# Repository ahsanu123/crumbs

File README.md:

- Hardware Status ✔️ Production Done
- Hardware Status 🏁 Prototype Done
- Software Status ☑️ Finished
- Software Status ⭐ POC only
- ⏳ In Progress

| Name                                                     | Hardware Status  | Software Status | Enclosure       | 
|----------------------------------------------------------|------------------|-----------------|-----------------|
|  TMD - Temperature Measurement Dongle                    |       🏁         |       ⭐        |     ⏳          |

## References 

- [ESP32 S3 Series IO MUX Map](https://documentation.espressif.com/esp32-s3_datasheet_en.pdf)
- [Emi's Reverse Engineer HCSR04](https://uglyduck.vajn.icu/ep/archive/2014/01/Making_a_better_HC_SR04_Echo_Locator.html)

<sub>a long project with the hope of completion. created with ♥️ by ah...</sub>

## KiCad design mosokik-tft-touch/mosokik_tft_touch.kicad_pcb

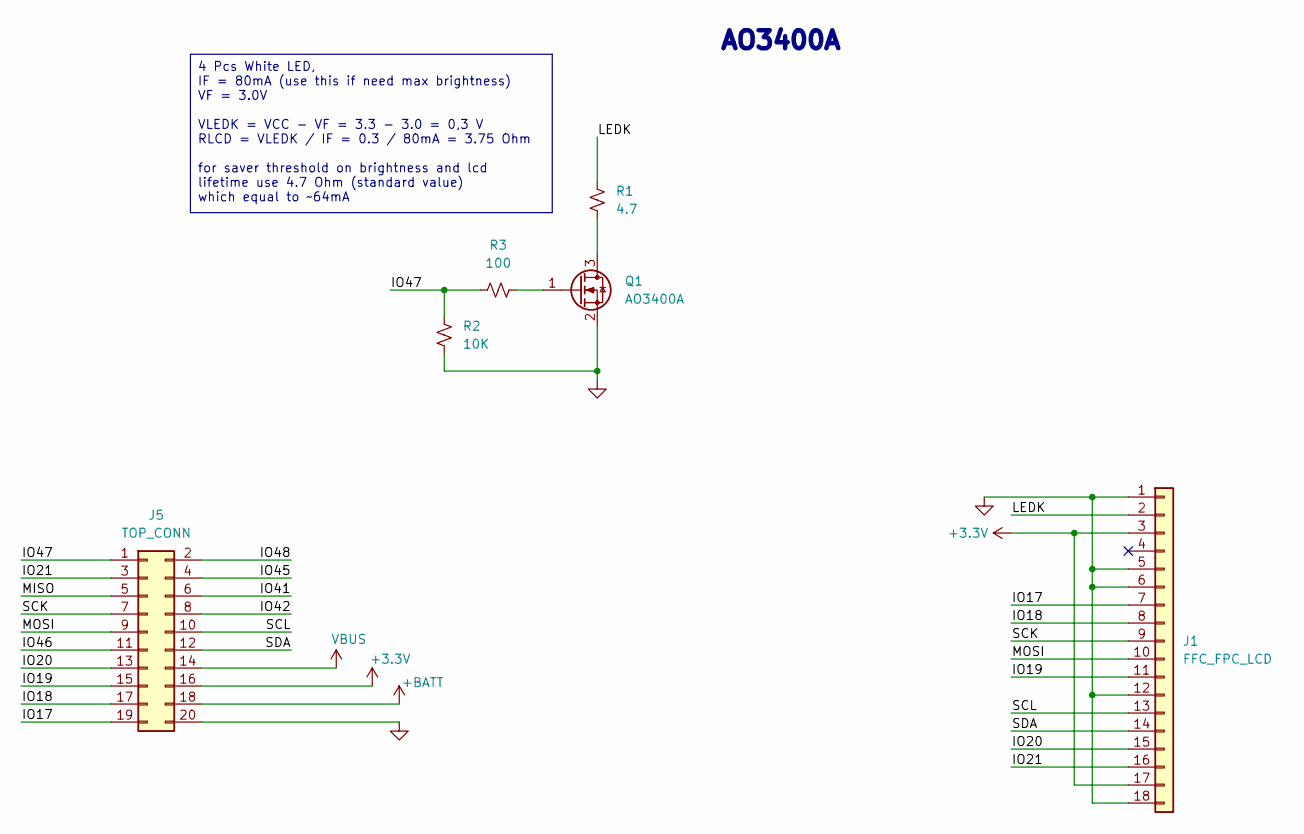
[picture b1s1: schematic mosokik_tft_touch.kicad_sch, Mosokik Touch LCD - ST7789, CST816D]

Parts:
J1: FFC_FPC_LCD; Hirose_FH12-18S-0.5SH_1x18-1MP_P0.50mm_Horizontal
J5: TOP_CONN; PinHeader_2x10_P2.54mm_Horizontal
Q1: AO3400A; SOT-23
R1: 4.7; R_0805_2012Metric
R2: 10K; R_0805_2012Metric
R3: 100; R_0805_2012Metric

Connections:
+3.3V: J1.3, J1.17, J5.16
+BATT: J5.18
/IO17: J1.7, J5.19
/IO18: J1.8, J5.17
/IO19: J1.11, J5.15
/IO20: J1.15, J5.13
/IO21: J1.16, J5.3
/IO41: J5.6
/IO42: J5.8
/IO45: J5.4
/IO46: J5.11
/IO47: J5.1, R2.1, R3.1
/IO48: J5.2
/LEDK: J1.2, R1.1
/MISO: J5.5
/MOSI: J1.10, J5.9
/SCK: J1.9, J5.7
/SCL: J1.13, J5.10
/SDA: J1.14, J5.12
GND: J1.1, J1.5, J1.6, J1.12, J1.18, J5.20, Q1.2 (S), R2.2
unnamed: Q1.3 (D), R1.2
unnamed: Q1.1 (G), R3.2
VBUS: J5.14

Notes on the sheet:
AO3400A
4 Pcs White LED, IF = 80mA (use this if need max brightness) VF = 3.0V VLEDK = VCC - VF = 3.3 - 3.0 = 0,3 V RLCD = VLEDK / IF = 0.3 / 80mA = 3.75 Ohm for saver threshold on brightness and lcd lifetime use 4.7 Ohm (standard value) which equal to ~64mA

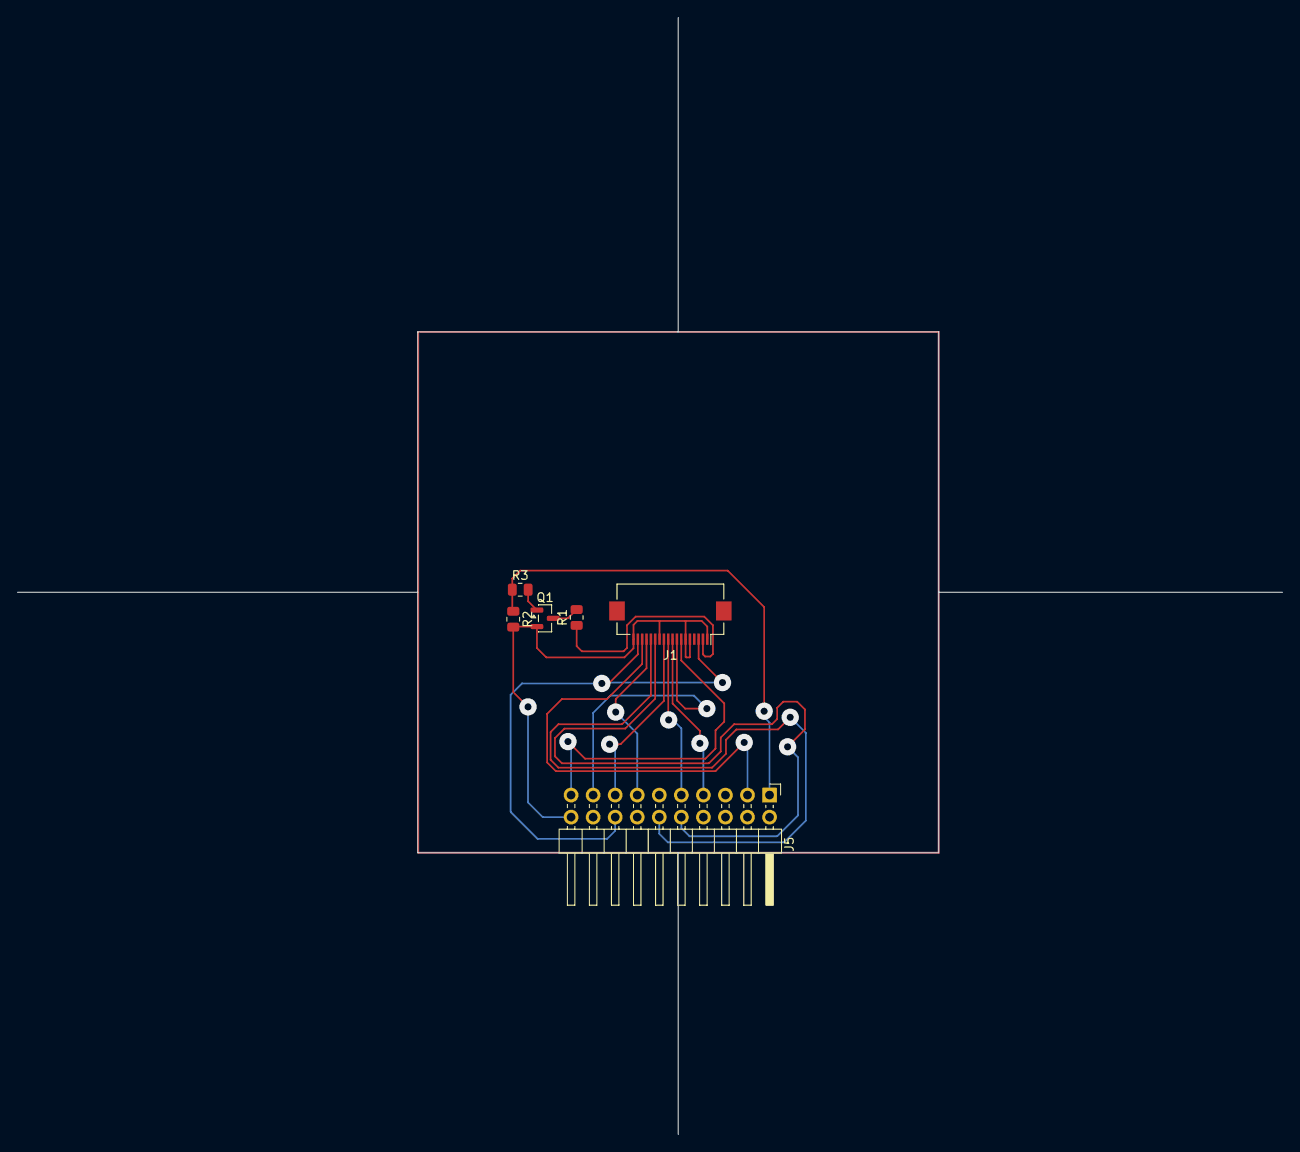
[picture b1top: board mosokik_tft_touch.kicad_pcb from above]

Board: 2 copper layers, 60.0 x 60.0 mm, 6 parts (0 on the bottom side), 15 nets.

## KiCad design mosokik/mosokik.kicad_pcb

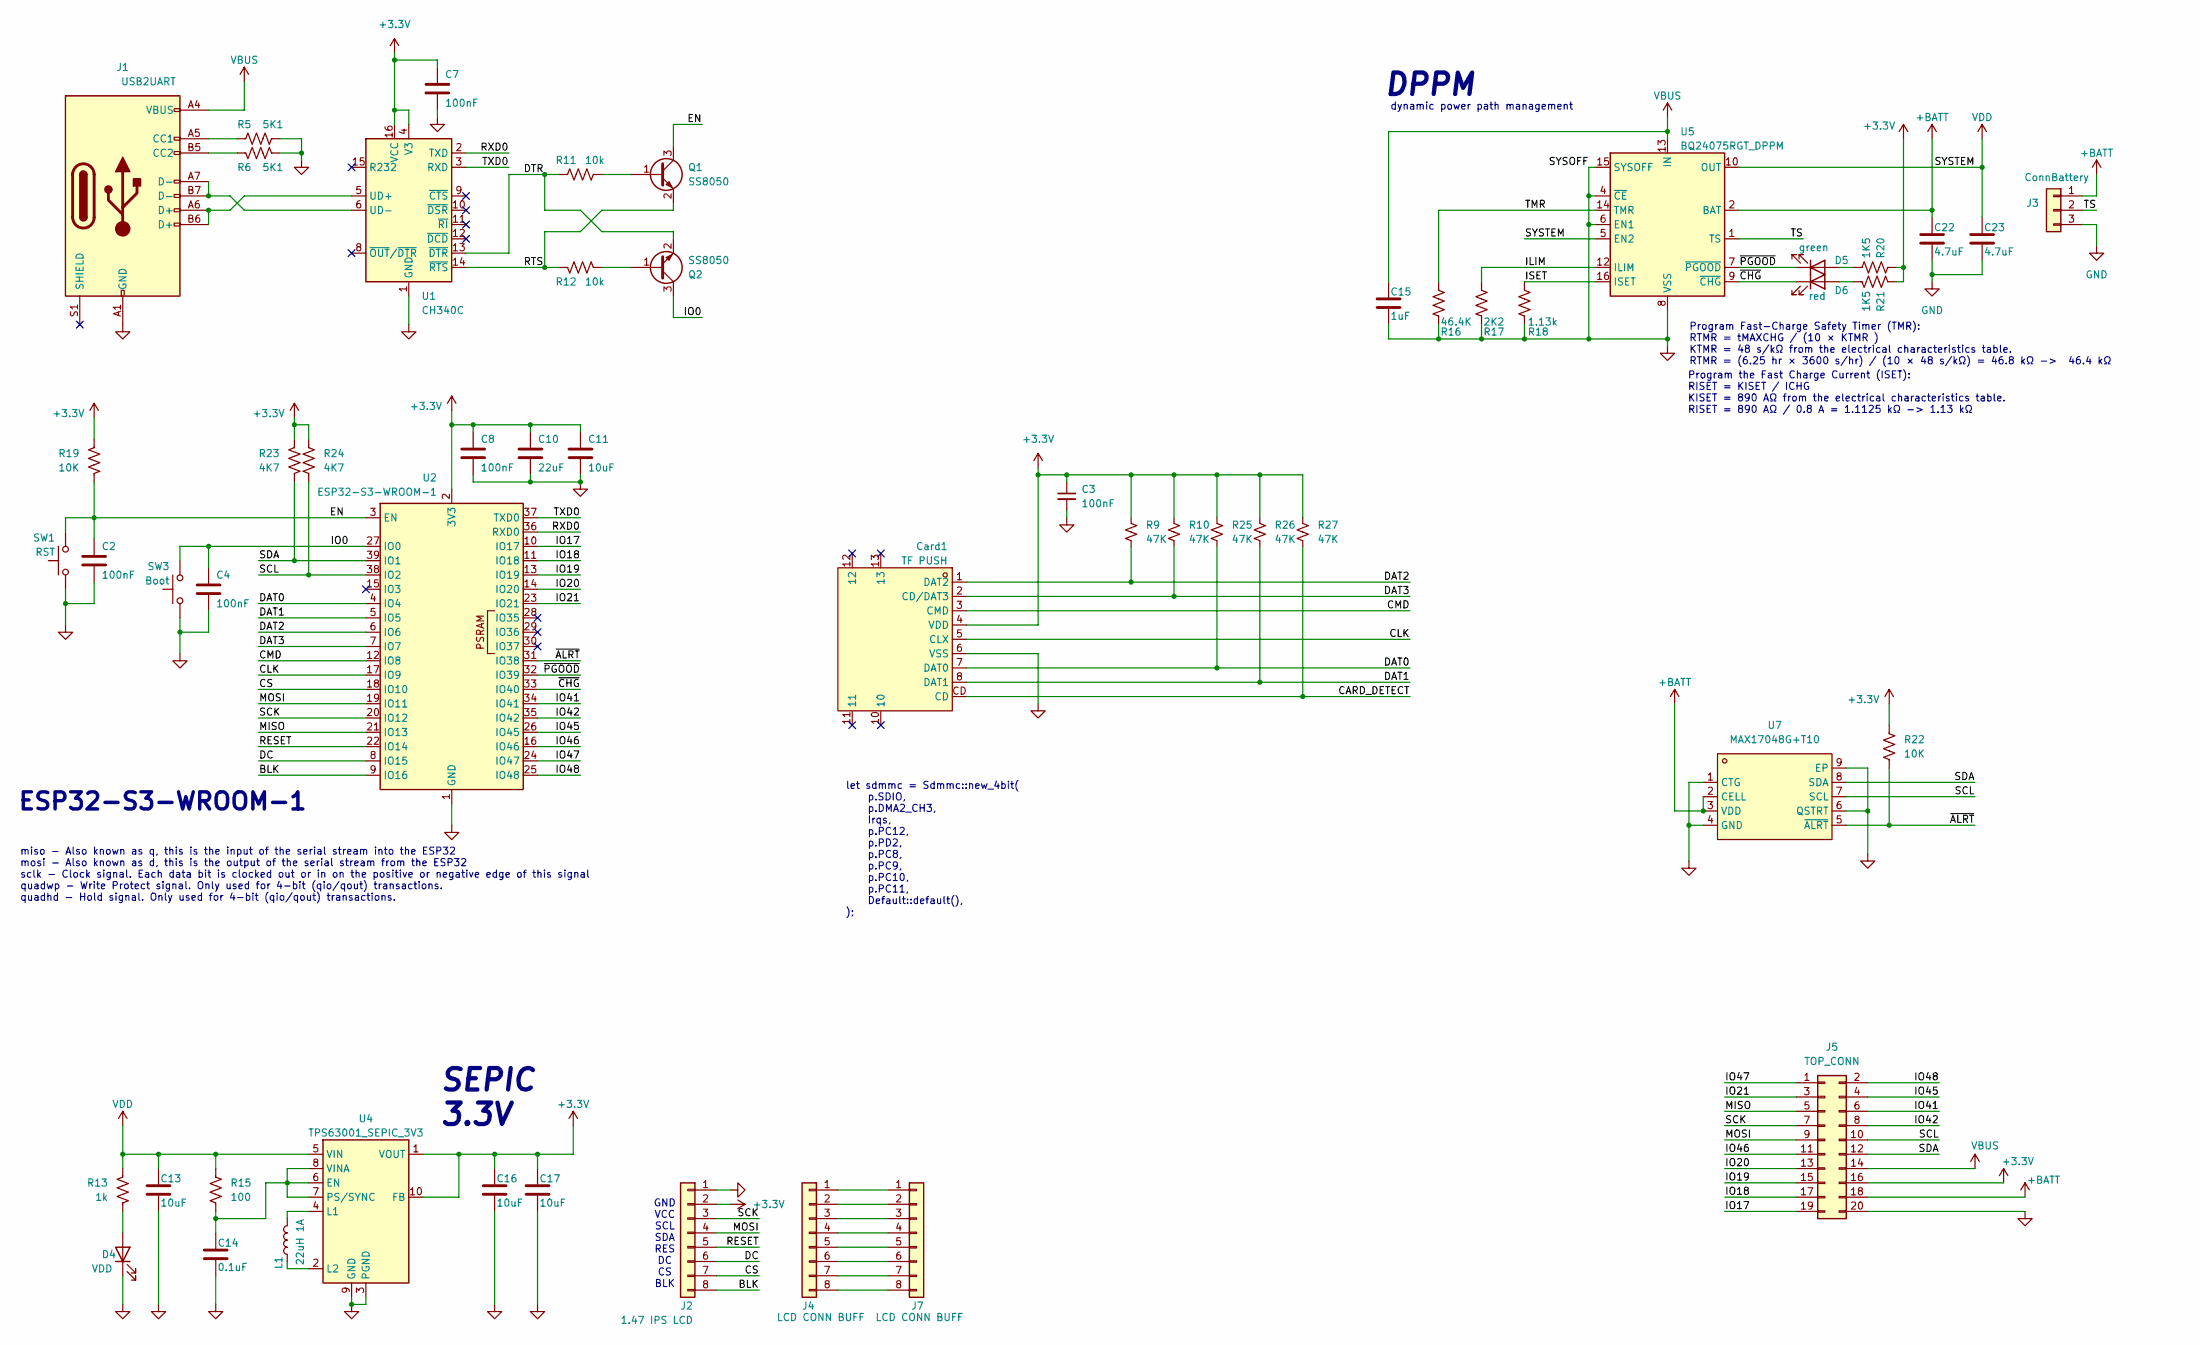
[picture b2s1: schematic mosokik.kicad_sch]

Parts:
C2, C4, C7, C8: 100nF; C_0805_2012Metric_Pad1.18x1.45mm_HandSolder
C3: 100nF; C_0805_2012Metric
C10: 22uF; C_0805_2012Metric_Pad1.18x1.45mm_HandSolder
C11, C13, C16, C17: 10uF; C_0805_2012Metric_Pad1.18x1.45mm_HandSolder
C14: 0.1uF; C_0805_2012Metric_Pad1.18x1.45mm_HandSolder
C15: 1uF; C_0805_2012Metric_Pad1.18x1.45mm_HandSolder
C22, C23: 4.7uF; C_0805_2012Metric_Pad1.18x1.45mm_HandSolder
Card1: TF PUSH; TF-SMD_TF-PUSH; MPN TF PUSH; LCSC Part C393941
D4: VDD; LED_1206_3216Metric_Pad1.42x1.75mm_HandSolder
D5: green; LED_0805_2012Metric_Pad1.15x1.40mm_HandSolder
D6: red; LED_0805_2012Metric_Pad1.15x1.40mm_HandSolder
J1: USB2UART; USB_C_Receptacle_GCT_USB4110
J2: 1.47 IPS LCD; PinHeader_1x08_P2.54mm_Vertical
J3: ConnBattery; PinHeader_1x03_P2.54mm_Vertical
J4, J7: LCD CONN BUFF; PinHeader_1x08_P2.54mm_Vertical
J5: TOP_CONN; PinHeader_2x10_P2.54mm_Horizontal
L1: 22uH 1A; L_Bourns_SRP7028A_7.3x6.6mm
Q1, Q2: SS8050; SOT-23_Handsoldering
R5, R6: 5K1; R_0805_2012Metric_Pad1.20x1.40mm_HandSolder
R9, R10, R25, R26, R27: 47K; R_0805_2012Metric
R11, R12: 10k; R_0805_2012Metric_Pad1.20x1.40mm_HandSolder
R13: 1k; R_0805_2012Metric_Pad1.20x1.40mm_HandSolder
R15: 100; R_0805_2012Metric_Pad1.20x1.40mm_HandSolder
R16: 46.4K; R_0805_2012Metric_Pad1.20x1.40mm_HandSolder
R17: 2K2; R_0805_2012Metric_Pad1.20x1.40mm_HandSolder
R18: 1.13k; R_0805_2012Metric_Pad1.20x1.40mm_HandSolder
R19, R22: 10K; R_0805_2012Metric_Pad1.20x1.40mm_HandSolder
R20, R21: 1K5; R_0805_2012Metric_Pad1.20x1.40mm_HandSolder
R23, R24: 4K7; R_0805_2012Metric_Pad1.20x1.40mm_HandSolder
SW1: RST; SW_SPST_PTS810
SW3: Boot; SW_SPST_PTS810
U1: CH340C; SOIC-16_3.9x9.9mm_P1.27mm
U2: ESP32-S3-WROOM-1
U4: TPS63001_SEPIC_3V3; Texas_DRC0010J_ThermalVias
U5: BQ24075RGT_DPPM; VQFN-16-1EP_3x3mm_P0.5mm_EP1.6x1.6mm
U7: MAX17048G+T10; TDFN-8_L2.0-W2.0-P0.50-BL-EP1.2; MPN MAX17048G+T10; LCSC Part C2682616

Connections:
+3.3V: C3.1, C7.1, C8.1, C10.1, C11.1, C16.1, C17.1, Card1.4 (VDD), J2.2, J5.16, R9.1, R10.1, R19.1, R20.2, R21.2, R22.1, R23.1, R24.1, R25.1, R26.1, R27.1, U1.4 (V3), U1.16 (VCC), U2.2 (3V3), U4.1 (VOUT), U4.10 (FB)
+BATT: C22.1, J3.1, J5.18, U5.2 (BAT), U5.3 (BAT), U7.2 (CELL), U7.3 (VDD)
/BLK: J2.8, U2.9 (IO16)
/CARD_DETECT: Card1.CD, R27.2
/CLK: Card1.5 (CLX), U2.17 (IO9)
/CMD: Card1.3 (CMD), U2.12 (IO8)
/CS: J2.7, U2.18 (IO10)
/DAT0: Card1.7 (DAT0), R25.2, U2.4 (IO4)
/DAT1: Card1.8 (DAT1), R26.2, U2.5 (IO5)
/DAT2: Card1.1 (DAT2), R9.2, U2.6 (IO6)
/DAT3: Card1.2 (CD/DAT3), R10.2, U2.7 (IO7)
/DC: J2.6, U2.8 (IO15)
/DTR: Q2.2 (E), R11.2, U1.13 (~DTR)
/EN: C2.1, Q1.3 (C), R19.2, SW1.2, U2.3 (EN)
/ILIM: R17.1, U5.12 (ILIM)
/IO0: C4.1, Q2.3 (C), SW3.2, U2.27 (IO0)
/IO17: J5.19, U2.10 (IO17)
/IO18: J5.17, U2.11 (IO18)
/IO19: J5.15, U2.13 (IO19)
/IO20: J5.13, U2.14 (IO20)
/IO21: J5.3, U2.23 (IO21)
/IO41: J5.6, U2.34 (IO41)
/IO42: J5.8, U2.35 (IO42)
/IO45: J5.4, U2.26 (IO45)
/IO46: J5.11, U2.16 (IO46)
/IO47: J5.1, U2.24 (IO47)
/IO48: J5.2, U2.25 (IO48)
/ISET: R18.1, U5.16 (ISET)
/MISO: J5.5, U2.21 (IO13)
/MOSI: J2.4, J5.9, U2.19 (IO11)
/RESET: J2.5, U2.22 (IO14)
/RTS: Q1.2 (E), R12.2, U1.14 (~RTS)
/RXD0: U1.2 (TXD), U2.36 (RXD0)
/SCK: J2.3, J5.7, U2.20 (IO12)
/SCL: J5.10, R24.2, U2.38 (IO2), U7.7 (SCL)
/SDA: J5.12, R23.2, U2.39 (IO1), U7.8 (SDA)
/TMR: R16.1, U5.14 (TMR)
/TS: J3.2, U5.1 (TS)
/TXD0: U1.3 (RXD), U2.37 (TXD0)
/~ALRT: R22.2, U2.31 (IO38), U7.5 (~ALRT)
/~CHG: D6.1 (K), U2.33 (IO40), U5.9 (~CHG)
/~PGOOD: D5.1 (K), U2.32 (IO39), U5.7 (~PGOOD)
GND: C2.2, C3.2, C4.2, C7.2, C8.2, C10.2, C11.2, C13.2, C14.2, C15.2, C16.2, C17.2, C22.2, C23.2, Card1.6 (VSS), D4.1 (K), J1.A1 (GND), J1.A12 (GND), J1.B1 (GND), J1.B12 (GND), J2.1, J3.3, J5.20, R5.1, R6.1, R16.2, R17.2, R18.2, SW1.1, SW3.1, U1.1 (GND), U2.1 (GND), U2.40 (GND), U2.41 (GND), U4.3 (PGND), U4.9 (GND), U4.11 (PGND), U5.4 (~CE), U5.6 (EN1), U5.8 (VSS), U5.15 (SYSOFF), U5.17 (VSS), U7.1 (CTG), U7.4 (GND), U7.6 (QSTRT), U7.9 (EP)
unnamed: D4.2 (A), R13.2
unnamed: D5.2 (A), R20.1
unnamed: D6.2 (A), R21.1
unnamed: J1.A5 (CC1), R5.2
unnamed: J1.B5 (CC2), R6.2
unnamed: J4.1, J7.1
unnamed: J4.2, J7.2
unnamed: J4.3, J7.3
unnamed: J4.4, J7.4
unnamed: J4.5, J7.5
unnamed: J4.6, J7.6
unnamed: J4.7, J7.7
unnamed: J4.8, J7.8
unnamed: Q1.1 (B), R11.1
unnamed: Q2.1 (B), R12.1
unnamed: J1.A6 (D+), J1.B6 (D+), U1.5 (UD+)
unnamed: J1.A7 (D-), J1.B7 (D-), U1.6 (UD-)
unnamed: C14.1, R15.2, U4.6 (EN), U4.7 (PS/SYNC), U4.8 (VINA)
unnamed: L1.2, U4.4 (L1)
unnamed: L1.1, U4.2 (L2)
VBUS: C15.1, J1.A4 (VBUS), J1.A9 (VBUS), J1.B4 (VBUS), J1.B9 (VBUS), J5.14, U5.13 (IN)
VDD: C13.1, C23.1, R13.1, R15.1, U4.5 (VIN), U5.5 (EN2), U5.10 (OUT), U5.11 (OUT)

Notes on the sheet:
DPPM
let sdmmc = Sdmmc::new_4bit( p.SDIO, p.DMA2_CH3, Irqs, p.PC12, p.PD2, p.PC8, p.PC9, p.PC10, p.PC11, Default::default(), );
SEPIC 3.3V
miso - Also known as q, this is the input of the serial stream into the ESP32 mosi - Also known as d, this is the output of the serial stream from the ESP32 sclk - Clock signal. Each data bit is clocked out or in on the positive or negative edge of this signal quadwp - Write Protect signal. Only us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
GND VCC SCL SDA RES DC CS BLK
Program Fast-Charge Safety Timer (TMR): RTMR = tMAXCHG / (10 × KTMR ) KTMR = 48 s/kΩ from the electrical characteristics table. RTMR = (6.25 hr × 3600 s/hr) / (10 × 48 s/kΩ) = 46.8 kΩ -> 46.4 kΩ
Program the Fast Charge Current (ISET): RISET = KISET / ICHG KISET = 890 AΩ from the electrical characteristics table. RISET = 890 AΩ / 0.8 A = 1.1125 kΩ -> 1.13 kΩ
dynamic power path management
ESP32-S3-WROOM-1

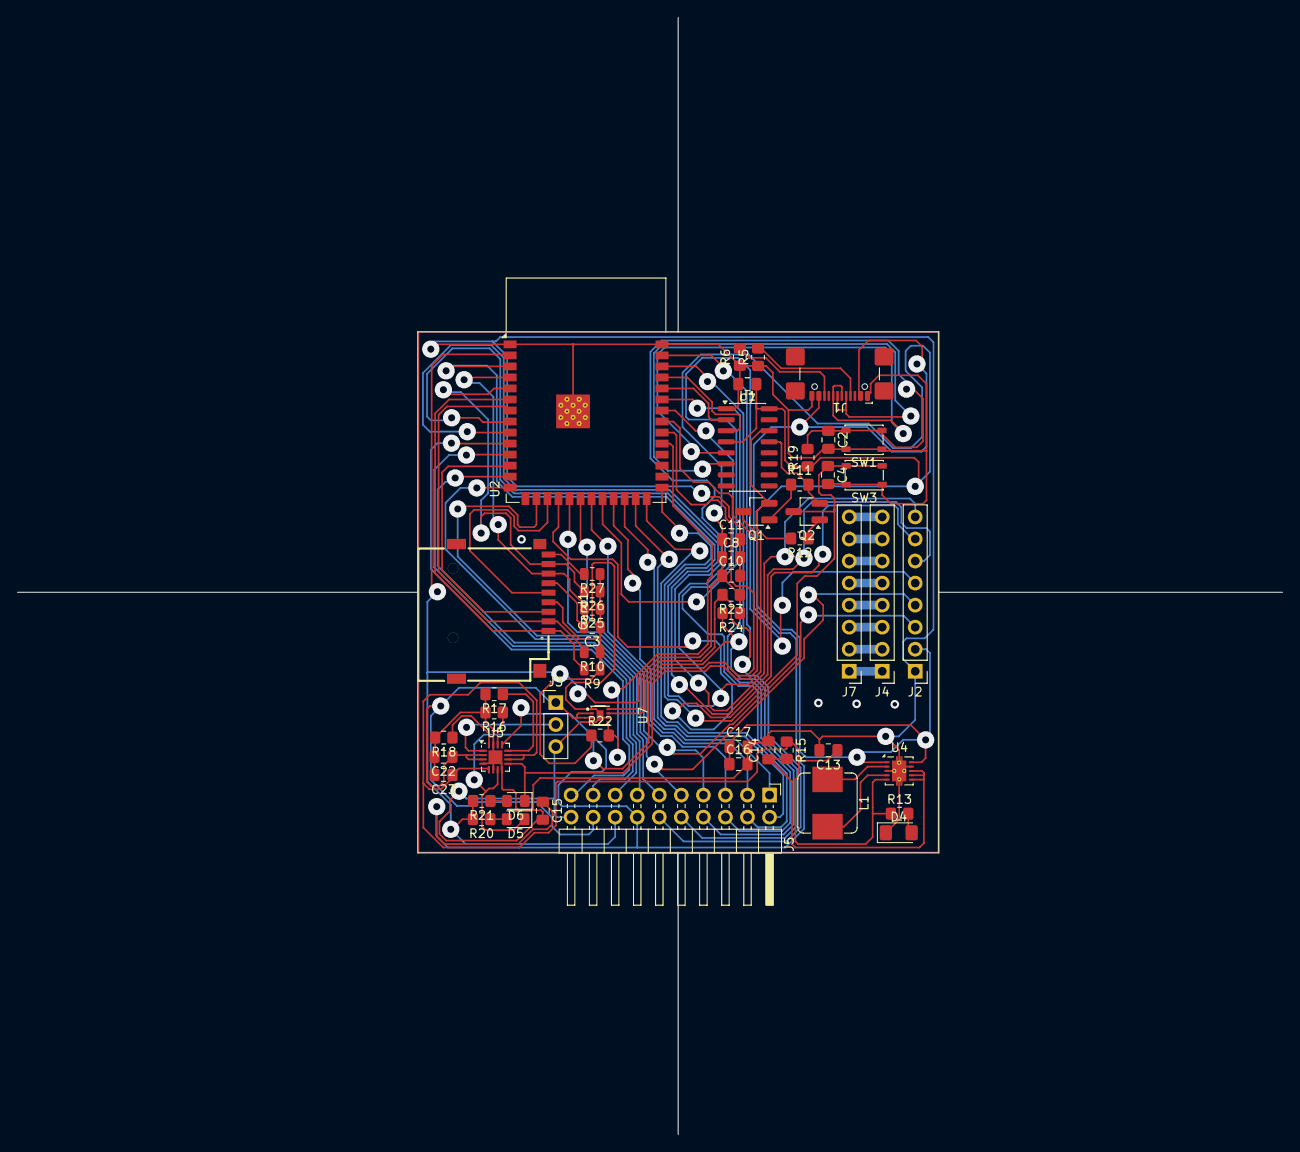
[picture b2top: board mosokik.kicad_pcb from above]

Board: 2 copper layers, 60.0 x 60.0 mm, 54 parts (0 on the bottom side), 65 nets.

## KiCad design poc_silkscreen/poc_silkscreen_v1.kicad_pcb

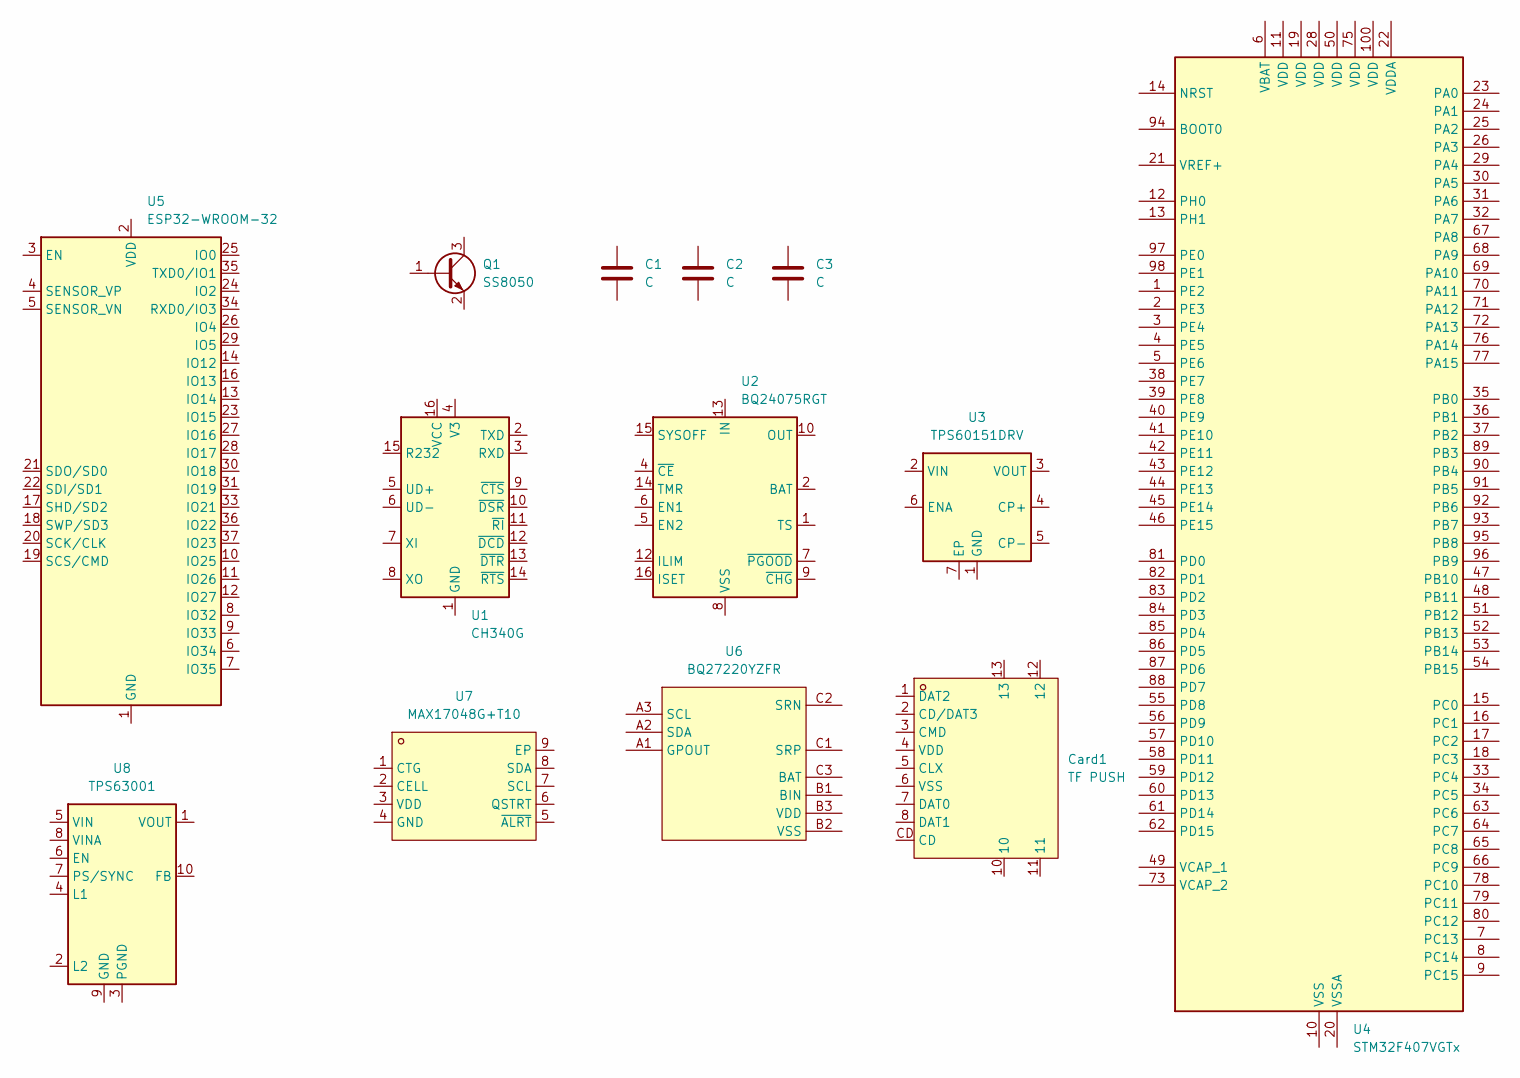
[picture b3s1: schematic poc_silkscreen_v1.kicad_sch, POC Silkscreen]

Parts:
C1: C; C_0603_1608Metric
C2: C; C_0805_2012Metric
C3: C; C_1210_3225Metric
Card1: TF PUSH; TF-SMD_TF-PUSH; MPN TF PUSH; LCSC Part C393941
Q1: SS8050; SOT-23
U1: CH340G; SOIC-16_3.9x9.9mm_P1.27mm
U2: BQ24075RGT; VQFN-16-1EP_3x3mm_P0.5mm_EP1.6x1.6mm
U3: TPS60151DRV; WSON-6-1EP_2x2mm_P0.65mm_EP1x1.6mm_ThermalVias
U4: STM32F407VGTx; LQFP-100_14x14mm_P0.5mm
U5: ESP32-WROOM-32
U6: BQ27220YZFR; DSBGA-9_L1.7-W1.6-R3-C3-P0.50-BL; MPN BQ27220YZFR; LCSC Part C528617
U7: MAX17048G+T10; TDFN-8_L2.0-W2.0-P0.50-BL-EP1.2; MPN MAX17048G+T10; LCSC Part C2682616
U8: TPS63001; Texas_DRC0010J_ThermalVias

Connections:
unnamed: U2.2 (BAT), U2.3 (BAT)
unnamed: U2.10 (OUT), U2.11 (OUT)
unnamed: U2.8 (VSS), U2.17 (VSS)
unnamed: U4.10 (VSS), U4.27 (VSS), U4.74 (VSS), U4.99 (VSS)
unnamed: U5.1 (GND), U5.15 (GND), U5.38 (GND), U5.39 (GND)
unnamed: U8.3 (PGND), U8.11 (PGND)

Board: 2 copper layers, 13 parts (0 on the bottom side), 6 nets, no tracks yet.

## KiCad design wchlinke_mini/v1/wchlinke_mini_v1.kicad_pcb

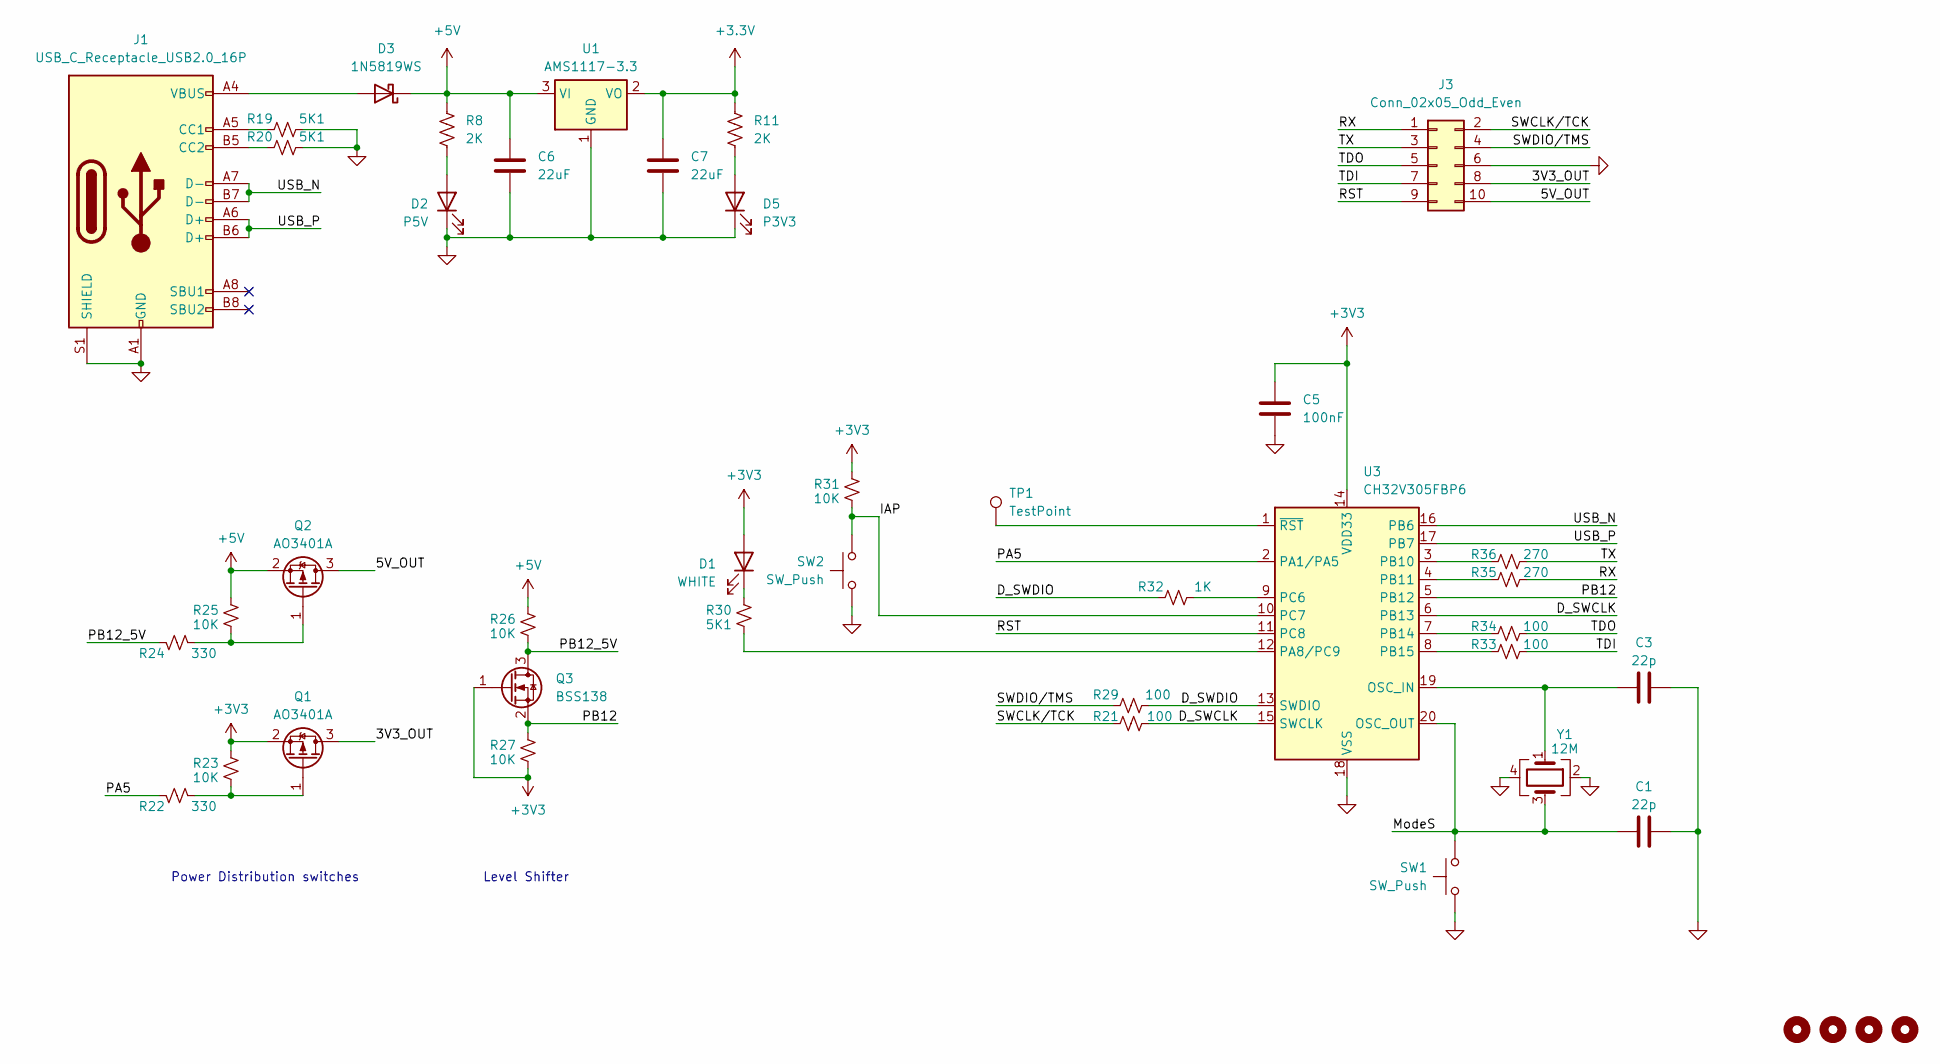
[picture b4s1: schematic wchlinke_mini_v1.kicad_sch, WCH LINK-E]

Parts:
C1, C3: 22p; C_0805_2012Metric_Pad1.18x1.45mm_HandSolder; LCSC Part # C1555
C5: 100nF; C_0805_2012Metric_Pad1.18x1.45mm_HandSolder; LCSC Part # C1525
C6, C7: 22uF; C_0805_2012Metric_Pad1.18x1.45mm_HandSolder
D1: WHITE; LED_1206_3216Metric_Pad1.42x1.75mm_HandSolder; LCSC Part # C2290
D2: P5V; LED_1206_3216Metric_Pad1.42x1.75mm_HandSolder
D3: 1N5819WS; D_SOD-323_HandSoldering; LCSC Part # C191023
D5: P3V3; LED_1206_3216Metric_Pad1.42x1.75mm_HandSolder
H1, H2, H3, H4: MountingHole; MountingHole_3.2mm_M3
J1: USB_C_Receptacle_USB2.0_16P; USB_C_Receptacle_GCT_USB4110; LCSC Part # C2988369
J3: Conn_02x05_Odd_Even; IDC-Header_2x05_P2.54mm_Horizontal
Q1, Q2: AO3401A; SOT-23; LCSC Part # C15127
Q3: BSS138; SOT-23; LCSC Part # C7420339
R8, R11: 2K; R_0805_2012Metric_Pad1.20x1.40mm_HandSolder
R19, R20, R30: 5K1; R_0805_2012Metric
R21, R29, R33, R34: 100; R_0805_2012Metric
R22, R24: 330; R_0805_2012Metric
R23, R25, R26, R27, R31: 10K; R_0805_2012Metric
R32: 1K; R_0805_2012Metric
R35, R36: 270; R_0805_2012Metric
SW1, SW2: SW_Push; SW_Push_1P1T_NO_CK_KMR2; LCSC Part # C720477
TP1: TestPoint; TestPoint_Pad_D1.5mm
U1: AMS1117-3.3; SOT-223-3_TabPin2
U3: CH32V305FBP6; TSSOP-20_4.4x6.5mm_P0.65mm; LCSC Part # C5123443
Y1: 12M; Crystal_SMD_3225-4Pin_3.2x2.5mm; LCSC Part # C9002

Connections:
+3.3V: C7.1, R11.1, U1.2 (VO)
+3V3: C5.1, D1.2 (A), Q1.2 (S), Q3.1 (G), R23.2, R27.1, R31.2, U3.14 (VDD33)
+5V: C6.1, D3.1 (K), Q2.2 (S), R8.1, R25.2, R26.2, U1.3 (VI)
/3V3_OUT: J3.8, Q1.3 (D)
/5V_OUT: J3.10, Q2.3 (D)
/D_SWCLK: R21.2, U3.6 (PB13), U3.15 (SWCLK)
/D_SWDIO: R29.2, R32.1, U3.13 (SWDIO)
/IAP: R31.1, SW2.1, U3.10 (PC7)
/ModeS: C1.2, SW1.1, U3.20 (OSC_OUT), Y1.3
/PA5: R22.1, U3.2 (PA1/PA5)
/PB12: Q3.2 (S), R27.2, U3.5 (PB12)
/PB12_5V: Q3.3 (D), R24.1, R26.1
/RST: J3.9, U3.11 (PC8)
/RX: J3.1, R35.2
/SWCLK/TCK: J3.2, R21.1
/SWDIO/TMS: J3.4, R29.1
/TDI: J3.7, R33.2
/TDO: J3.5, R34.2
/TX: J3.3, R36.2
/USB_N: J1.A7 (D-), J1.B7 (D-), U3.16 (PB6)
/USB_P: J1.A6 (D+), J1.B6 (D+), U3.17 (PB7)
GND: C1.1, C3.1, C5.2, C6.2, C7.2, D2.1 (K), D5.1 (K), J1.A1 (GND), J1.A12 (GND), J1.B1 (GND), J1.B12 (GND), J1.S1 (SHIELD), J3.6, R19.2, R20.2, SW1.2, SW2.2, U1.1 (GND), U3.18 (VSS), Y1.2, Y1.4
unnamed: D1.1 (K), R30.2
unnamed: D2.2 (A), R8.2
unnamed: D3.2 (A), J1.A4 (VBUS), J1.A9 (VBUS), J1.B4 (VBUS), J1.B9 (VBUS)
unnamed: D5.2 (A), R11.2
unnamed: J1.A5 (CC1), R19.1
unnamed: J1.B5 (CC2), R20.1
unnamed: Q1.1 (G), R22.2, R23.1
unnamed: Q2.1 (G), R24.2, R25.1
unnamed: C3.2, U3.19 (OSC_IN), Y1.1
unnamed: R30.1, U3.12 (PA8/PC9)
unnamed: R36.1, U3.3 (PB10)
unnamed: R35.1, U3.4 (PB11)
unnamed: R34.1, U3.7 (PB14)
unnamed: R33.1, U3.8 (PB15)
unnamed: R32.2, U3.9 (PC6)
unnamed: TP1.1 (1_1), U3.1 (~RST)

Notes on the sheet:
Power Distribution switches
Level Shifter

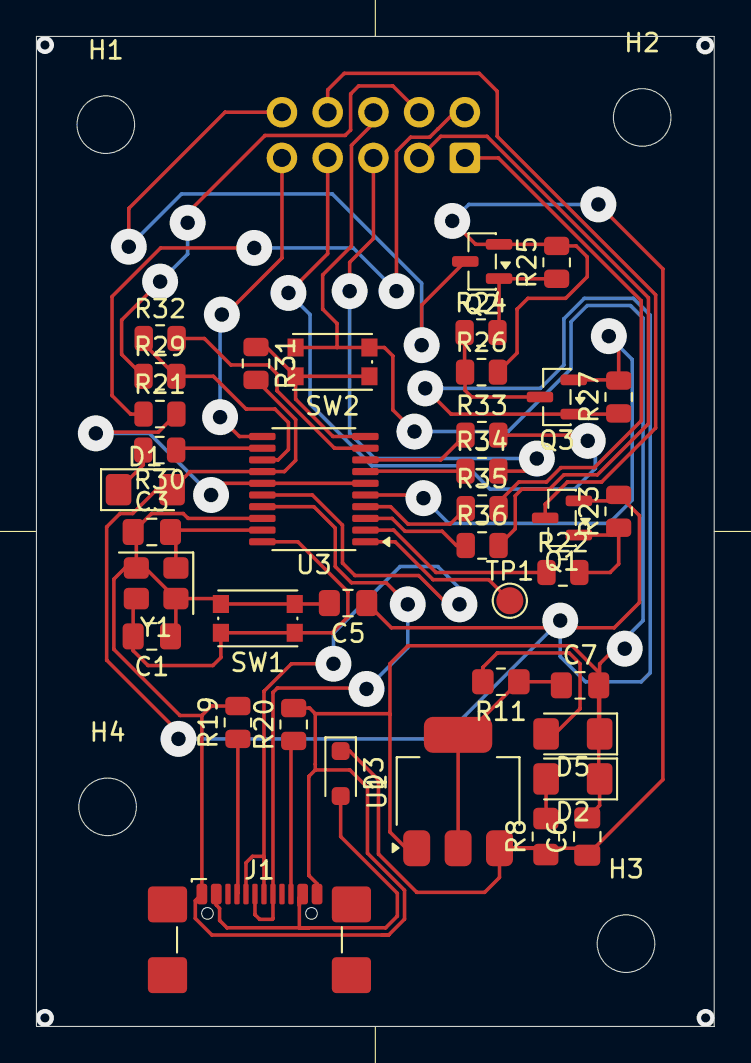
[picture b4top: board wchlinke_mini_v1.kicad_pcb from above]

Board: 2 copper layers, 37.7 x 55.0 mm, 43 parts (1 on the bottom side), 38 nets.
